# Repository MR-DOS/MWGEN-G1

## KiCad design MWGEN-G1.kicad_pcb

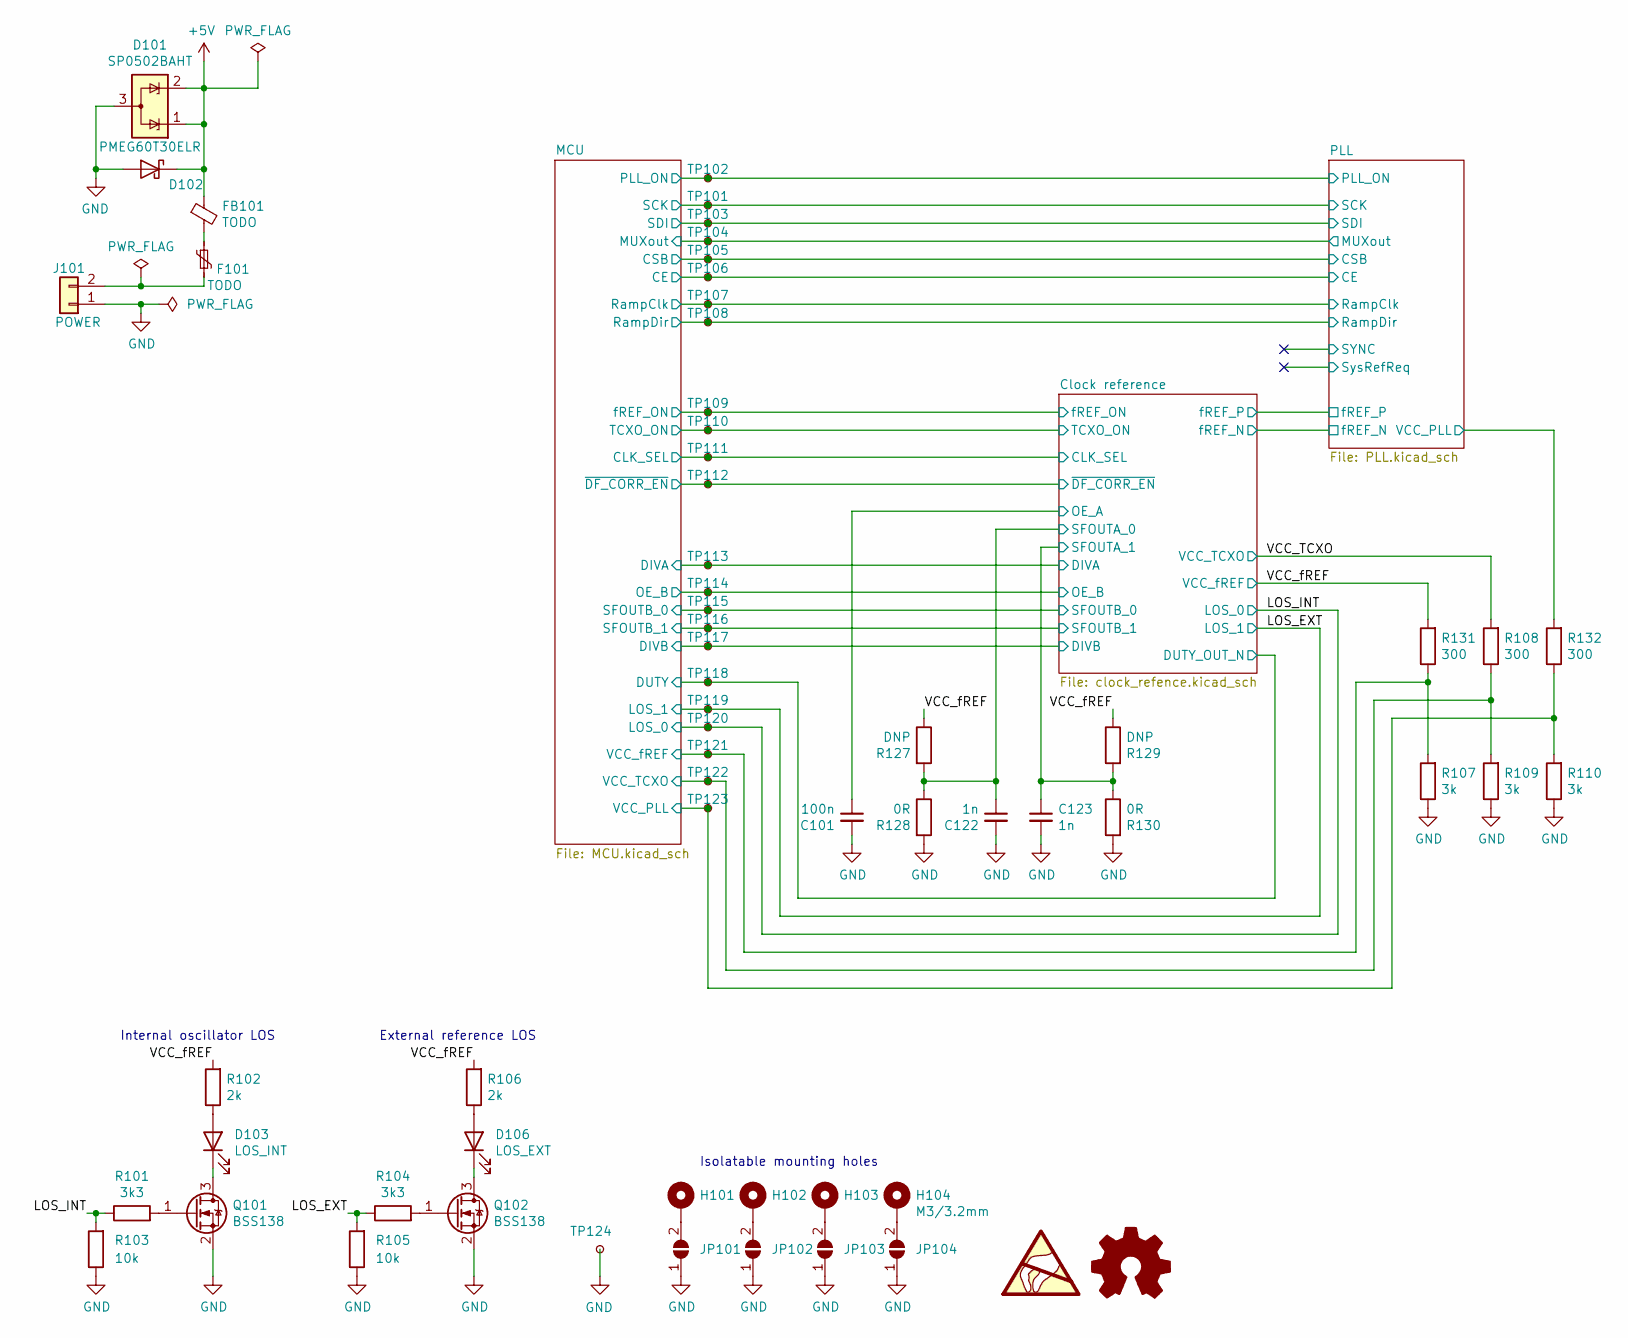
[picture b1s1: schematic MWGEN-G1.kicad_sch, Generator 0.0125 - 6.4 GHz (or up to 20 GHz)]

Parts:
C101: 100n; C_0603_1608Metric_Pad1.08x0.95mm_HandSolder
C122, C123: 1n; C_0603_1608Metric_Pad1.08x0.95mm_HandSolder
D101: SP0502BAHT; SOT-23
D102: PMEG60T30ELR; Nexperia_CFP3_SOD-123W
D103: LOS_INT; LED_0603_1608Metric_Pad1.05x0.95mm_HandSolder
D106: LOS_EXT; LED_0603_1608Metric_Pad1.05x0.95mm_HandSolder
F101: TODO; Fuse_2920_7451Metric_Pad2.10x5.45mm_HandSolder
FB101: TODO; L_0805_2012Metric_Pad1.05x1.20mm_HandSolder
H101, H102, H103, H104: M3/3.2mm; MountingHole_3.2mm_M3_Pad_Via
J101: POWER; PhoenixContact_MSTBA_2,5_2-G-5,08_1x02_P5.08mm_Horizontal
JP101, JP102, JP103, JP104: SolderJumper_2_Open; SolderJumper-2_P1.3mm_Open_TrianglePad1.0x1.5mm
Q101, Q102: BSS138; SOT-23
R101, R104: 3k3; R_0603_1608Metric_Pad0.98x0.95mm_HandSolder
R102, R106: 2k; R_0603_1608Metric_Pad0.98x0.95mm_HandSolder
R103, R105: 10k; R_0603_1608Metric_Pad0.98x0.95mm_HandSolder
R107, R109, R110: 3k; R_0603_1608Metric_Pad0.98x0.95mm_HandSolder
R108, R131, R132: 300; R_0603_1608Metric_Pad0.98x0.95mm_HandSolder
R127, R129: DNP; R_0603_1608Metric_Pad0.98x0.95mm_HandSolder
R128, R130: 0R; R_0603_1608Metric_Pad0.98x0.95mm_HandSolder
TP101, TP102, TP103, TP104, TP105, TP106, TP107, TP108, TP109, TP110, TP111, TP112, TP113, TP114, TP115, TP116, TP117, TP118, TP119, TP120, TP121, TP122, TP123, TP124: TestPoint_Small; TestPoint_Pad_D1.0mm

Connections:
+5V: D101.1 (K), D101.2 (K), D102.1 (K), FB101.1; also elsewhere on the board
/Clock reference/CLK_SEL: TP111.1; also elsewhere on the board
/Clock reference/DIVA: TP113.1; also elsewhere on the board
/Clock reference/DIVB: TP117.1; also elsewhere on the board
/Clock reference/Input Clocks/DUTY_OUT_N: TP118.1; also elsewhere on the board
/Clock reference/OE_A: C101.1; also elsewhere on the board
/Clock reference/OE_B: TP114.1; also elsewhere on the board
/Clock reference/SFOUTA_0: C122.1, R127.2, R128.1; also elsewhere on the board
/Clock reference/SFOUTA_1: C123.1, R129.2, R130.1; also elsewhere on the board
/Clock reference/SFOUTB_0: TP115.1; also elsewhere on the board
/Clock reference/SFOUTB_1: TP116.1; also elsewhere on the board
/Clock reference/TCXO_ON: TP110.1; also elsewhere on the board
/Clock reference/fREF_ON: TP109.1; also elsewhere on the board
/Clock reference/~DF_CORR_EN: TP112.1; also elsewhere on the board
/LOS_EXT: R104.1, R105.2, TP119.1; also elsewhere on the board
/LOS_INT: R101.1, R103.2, TP120.1; also elsewhere on the board
/MCU/CE: TP106.1; also elsewhere on the board
/MCU/CSB: TP105.1; also elsewhere on the board
/MCU/MUXout: TP104.1; also elsewhere on the board
/MCU/PLL_ON: TP102.1; also elsewhere on the board
/MCU/RampClk: TP107.1; also elsewhere on the board
/MCU/RampDir: TP108.1; also elsewhere on the board
/MCU/SCK: TP101.1; also elsewhere on the board
/MCU/SDI: TP103.1; also elsewhere on the board
/MCU/VCC_PLL: R110.2, R132.1, TP123.1; also elsewhere on the board
/MCU/VCC_TCXO: R108.1, R109.2, TP122.1; also elsewhere on the board
/MCU/VCC_fREF: R107.2, R131.1, TP121.1; also elsewhere on the board
/PLL/VCC_PLL: R132.2; also elsewhere on the board
/VCC_TCXO: R108.2; also elsewhere on the board
GND: C101.2, C122.2, C123.2, D101.3 (A), D102.2 (A), J101.1, JP101.1 (A), JP102.1 (A), JP103.1 (A), JP104.1 (A), Q101.2 (S), Q102.2 (S), R103.1, R105.1, R107.1, R109.1, R110.1, R128.2, R130.2, TP124.1; also elsewhere on the board
unnamed: D103.1 (K), Q101.3 (D)
unnamed: D103.2 (A), R102.1
unnamed: D106.1 (K), Q102.3 (D)
unnamed: D106.2 (A), R106.1
unnamed: F101.1, FB101.2
unnamed: F101.2, J101.2
unnamed: H101.1, JP101.2 (B)
unnamed: H102.1, JP102.2 (B)
unnamed: H103.1, JP103.2 (B)
unnamed: H104.1, JP104.2 (B)
unnamed: Q101.1 (G), R101.2
unnamed: Q102.1 (G), R104.2
VCC_fREF: R102.2, R106.2, R127.1, R129.1, R131.2; also elsewhere on the board

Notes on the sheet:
External reference LOS
Isolatable mounting holes
Internal oscillator LOS

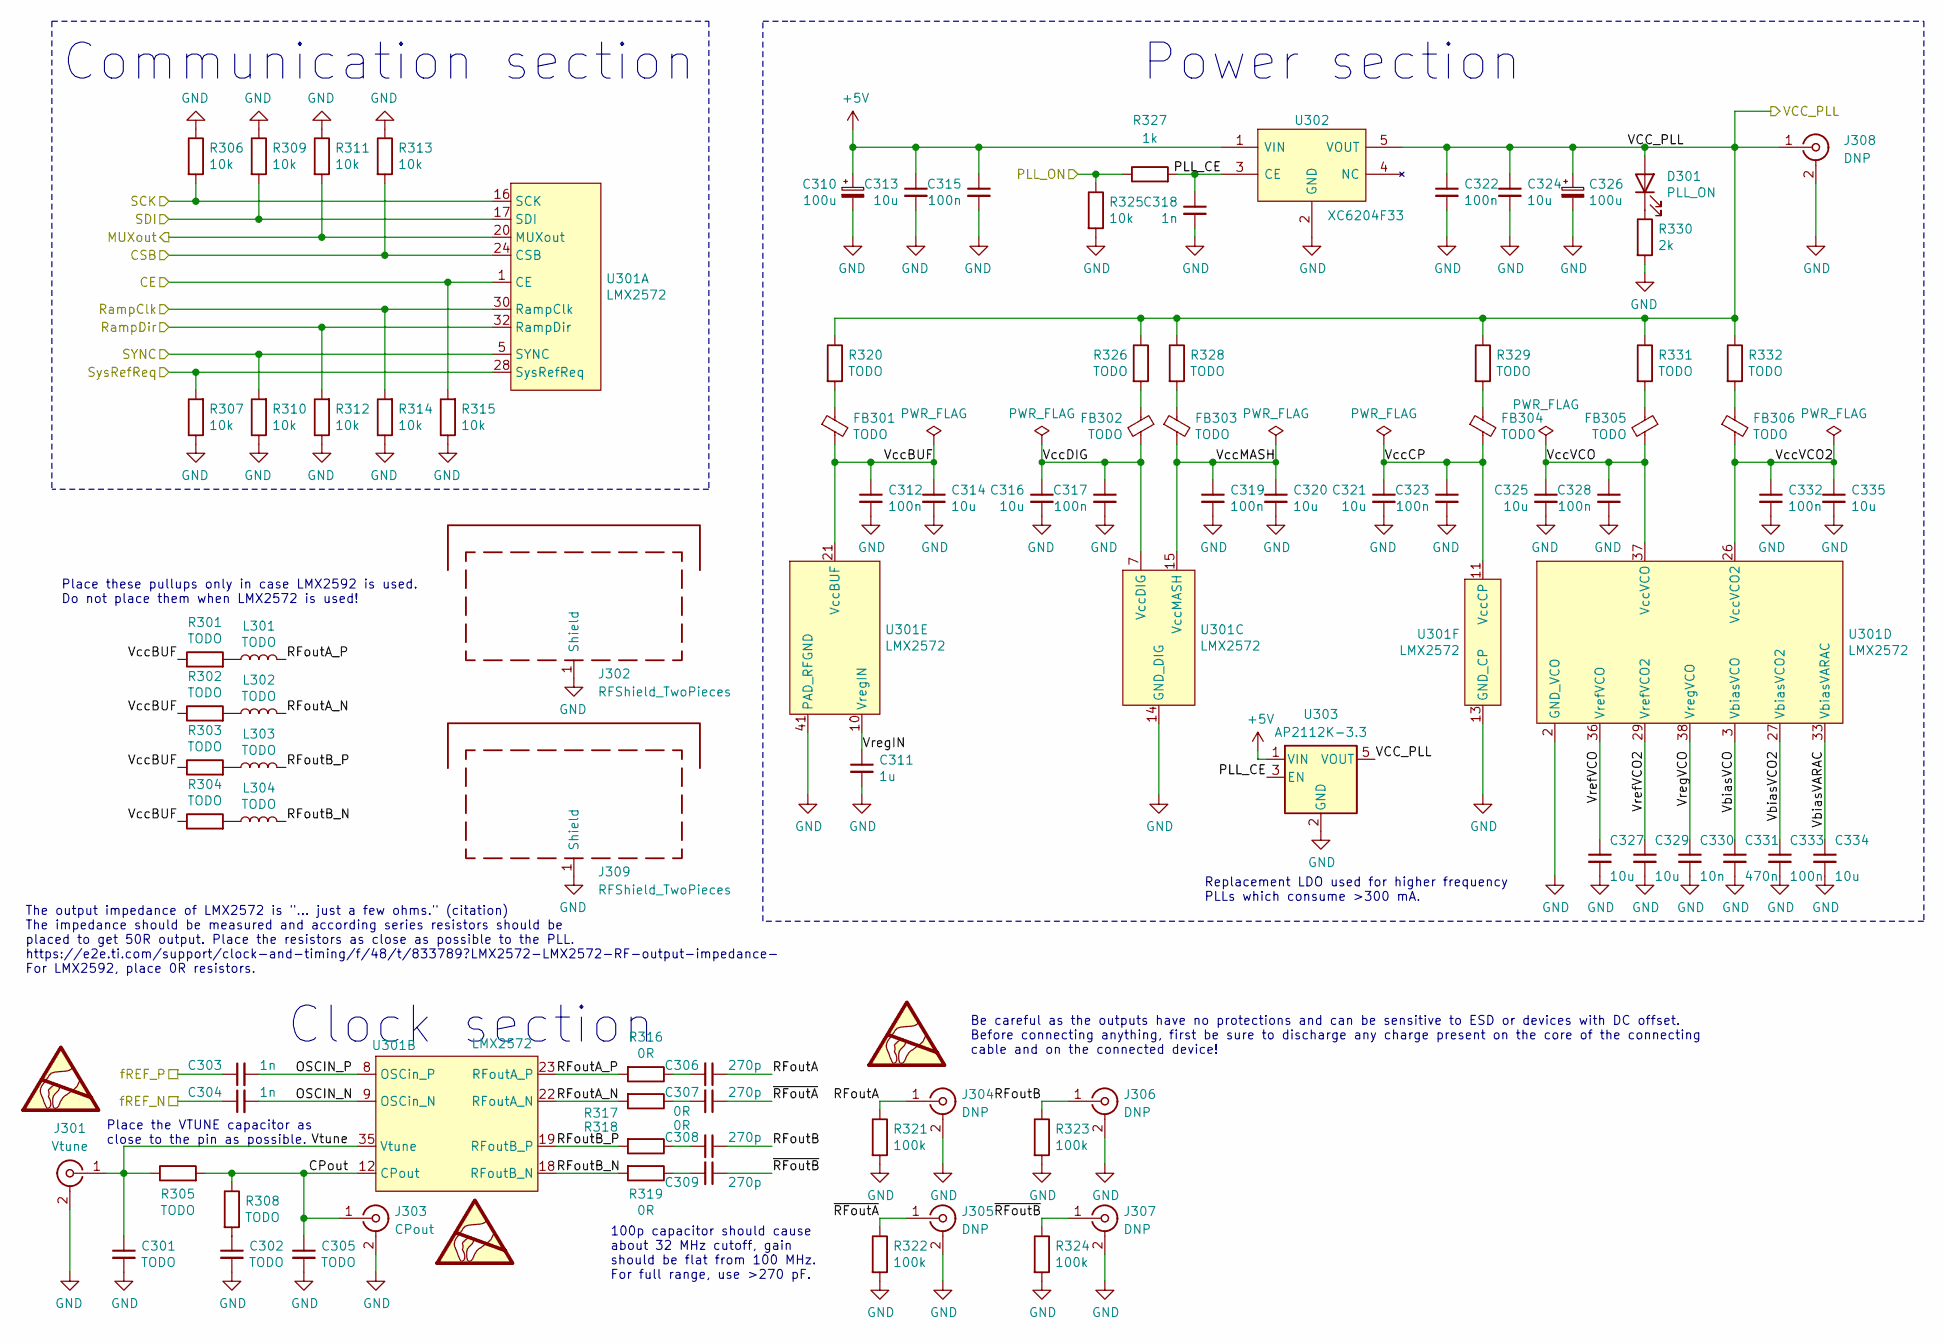
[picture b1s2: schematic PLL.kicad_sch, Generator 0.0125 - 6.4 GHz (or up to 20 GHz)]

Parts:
C301, C302, C305: TODO; C_0603_1608Metric_Pad1.08x0.95mm_HandSolder
C303, C304, C318: 1n; C_0603_1608Metric_Pad1.08x0.95mm_HandSolder
C306, C307, C308, C309: 270p; C_0603_1608Metric_Pad1.08x0.95mm_HandSolder
C310, C326: 100u; CP_Elec_6.3x5.8
C311: 1u; C_0603_1608Metric_Pad1.08x0.95mm_HandSolder
C312, C315, C317, C319, C322, C323, C328, C332, C333: 100n; C_0603_1608Metric_Pad1.08x0.95mm_HandSolder
C313, C314, C316, C320, C321, C324, C325, C327, C329, C334, C335: 10u; C_0805_2012Metric_Pad1.18x1.45mm_HandSolder
C330: 10n; C_0603_1608Metric_Pad1.08x0.95mm_HandSolder
C331: 470n; C_0603_1608Metric_Pad1.08x0.95mm_HandSolder
D301: PLL_ON; LED_0603_1608Metric_Pad1.05x0.95mm_HandSolder
FB301, FB302, FB303, FB304, FB305, FB306: TODO; L_0603_1608Metric_Pad1.05x0.95mm_HandSolder
J301: Vtune; U.FL_Molex_MCRF_73412-0110_Vertical
J302, J309: RFShield_TwoPieces; Laird_Technologies_BMI-S-205-F_38.10x25.40mm
J303: CPout; U.FL_Molex_MCRF_73412-0110_Vertical
J304, J305, J306, J307: DNP; SMA_rosenberger_hybrid
J308: DNP; U.FL_Molex_MCRF_73412-0110_Vertical
L301, L302, L303, L304: TODO; L_0603_1608Metric_Pad1.05x0.95mm_HandSolder
R301, R302, R303, R304, R305, R308, R320, R326, R328, R329, R331, R332: TODO; R_0603_1608Metric_Pad0.98x0.95mm_HandSolder
R306, R307, R309, R310, R311, R312, R313, R314, R315, R325: 10k; R_0603_1608Metric_Pad0.98x0.95mm_HandSolder
R316, R317, R318, R319: 0R; R_0603_1608Metric_Pad0.98x0.95mm_HandSolder
R321, R322, R323, R324: 100k; R_0603_1608Metric_Pad0.98x0.95mm_HandSolder
R327: 1k; R_0603_1608Metric_Pad0.98x0.95mm_HandSolder
R330: 2k; R_0603_1608Metric_Pad0.98x0.95mm_HandSolder
U301: LMX2572; QFN-40_EP_6x6_Pitch0.5mm_LMX2572
U302: XC6204F33; SOT-89-5_Handsoldering
U303: AP2112K-3.3; SOT-23-5

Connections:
+5V: C310.1, C313.1, C315.1, U302.1 (VIN), U303.1 (VIN); also elsewhere on the board
/Clock reference/fREF_N: C304.1; also elsewhere on the board
/Clock reference/fREF_P: C303.1; also elsewhere on the board
/MCU/CE: R315.2, U301.1 (CE); also elsewhere on the board
/MCU/CSB: R313.2, U301.24 (CSB); also elsewhere on the board
/MCU/MUXout: R311.2, U301.20 (MUXout); also elsewhere on the board
/MCU/PLL_ON: R325.1, R327.1; also elsewhere on the board
/MCU/RampClk: R314.2, U301.30 (RampClk); also elsewhere on the board
/MCU/RampDir: R312.2, U301.32 (RampDir); also elsewhere on the board
/MCU/SCK: R306.2, U301.16 (SCK); also elsewhere on the board
/MCU/SDI: R309.2, U301.17 (SDI); also elsewhere on the board
/PLL/CPout: C305.1, J303.1 (In), R305.2, R308.1, U301.12 (CPout)
/PLL/OSCIN_N: C304.2, U301.9 (OSCin_N)
/PLL/OSCIN_P: C303.2, U301.8 (OSCin_P)
/PLL/RFoutA: C306.1, J304.1 (In), R321.1
/PLL/RFoutA_N: L302.2, R317.2, U301.22 (RFoutA_N)
/PLL/RFoutA_P: L301.2, R316.2, U301.23 (RFoutA_P)
/PLL/RFoutB: C308.1, J306.1 (In), R323.1
/PLL/RFoutB_N: L304.2, R319.2, U301.18 (RFoutB_N)
/PLL/RFoutB_P: L303.2, R318.2, U301.19 (RFoutB_P)
/PLL/SYNC: R310.2, U301.5 (SYNC)
/PLL/SysRefReq: R307.2, U301.28 (SysRefReq)
/PLL/VCC_PLL: C322.1, C324.1, C326.1, D301.2 (A), J308.1 (In), R320.1, R326.1, R328.1, R329.1, R331.1, R332.1, U302.5 (VOUT), U303.5 (VOUT); also elsewhere on the board
/PLL/VbiasVARAC: C334.1, U301.33 (VbiasVARAC)
/PLL/VbiasVCO: C331.1, U301.3 (VbiasVCO)
/PLL/VbiasVCO2: C333.1, U301.27 (VbiasVCO2)
/PLL/VccBUF: C312.1, C314.1, FB301.2, R301.1, R302.1, R303.1, R304.1, U301.21 (VccBUF)
/PLL/VccCP: C321.1, C323.1, FB304.2, U301.11 (VccCP)
/PLL/VccDIG: C316.1, C317.1, FB302.2, U301.7 (VccDIG)
/PLL/VccMASH: C319.1, C320.1, FB303.2, U301.15 (VccMASH)
/PLL/VccVCO: C325.1, C328.1, FB305.2, U301.37 (VccVCO)
/PLL/VccVCO2: C332.1, C335.1, FB306.2, U301.26 (VccVCO2)
/PLL/VrefVCO: C327.1, U301.36 (VrefVCO)
/PLL/VrefVCO2: C329.1, U301.29 (VrefVCO2)
/PLL/VregIN: C311.1, U301.10 (VregIN)
/PLL/VregVCO: C330.1, U301.38 (VregVCO)
/PLL/Vtune: C301.1, J301.1 (In), R305.1, U301.35 (Vtune)
/PLL/~RFoutA: C307.1, J305.1 (In), R322.1
/PLL/~RFoutB: C309.1, J307.1 (In), R324.1
GND: C301.2, C302.2, C305.2, C310.2, C311.2, C312.2, C313.2, C314.2, C315.2, C316.2, C317.2, C318.2, C319.2, C320.2, C321.2, C322.2, C323.2, C324.2, C325.2, C326.2, C327.2, C328.2, C329.2, C330.2, C331.2, C332.2, C333.2, C334.2, C335.2, J301.2 (Ext), J302.1 (Shield), J303.2 (Ext), J304.2 (Ext), J305.2 (Ext), J306.2 (Ext), J307.2 (Ext), J308.2 (Ext), J309.1 (Shield), R306.1, R307.1, R309.1, R310.1, R311.1, R312.1, R313.1, R314.1, R315.1, R321.2, R322.2, R323.2, R324.2, R325.2, R330.2, U301.2 (GND_VCO), U301.4 (GND_VCO), U301.6 (GND_DIG), U301.13 (GND_CP), U301.14 (GND_DIG), U301.25 (GND_VCO), U301.31 (GND_VCO), U301.34 (GND_VCO), U301.39 (GND_VCO), U301.40 (GND_DIG), U301.41 (PAD_RFGND), U302.2 (GND), U303.2 (GND); also elsewhere on the board
unnamed: C302.1, R308.2
unnamed: C306.2, R316.1
unnamed: C307.2, R317.1
unnamed: C308.2, R318.1
unnamed: C309.2, R319.1
unnamed: C318.1, R327.2, U302.3 (CE), U303.3 (EN)
unnamed: D301.1 (K), R330.1
unnamed: FB301.1, R320.2
unnamed: FB302.1, R326.2
unnamed: FB303.1, R328.2
unnamed: FB304.1, R329.2
unnamed: FB305.1, R331.2
unnamed: FB306.1, R332.2
unnamed: L301.1, R301.2
unnamed: L302.1, R302.2
unnamed: L303.1, R303.2
unnamed: L304.1, R304.2

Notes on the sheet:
The output impedance of LMX2572 is "... just a few ohms." (citation) The impedance should be measured and according series resistors should be placed to get 50R output. Place the resistors as close as possible to the PLL. https://e2e.ti.com/support/clock-and-timing/f/48/t/833789?LMX2572-LMX2572-RF-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
Clock section
100p capacitor should cause about 32 MHz cutoff, gain should be flat from 100 MHz. For full range, use >270 pF.
Place these pullups only in case LMX2592 is used. Do not place them when LMX2572 is used!
Replacement LDO used for higher frequency PLLs which consume >300 mA.
Be careful as the outputs have no protections and can be sensitive to ESD or devices with DC offset. Before connecting anything, first be sure to discharge any charge present on the core of the connecting cable and on the connected device!
Place the VTUNE capacitor as close to the pin as possible.
Communication section
Power section

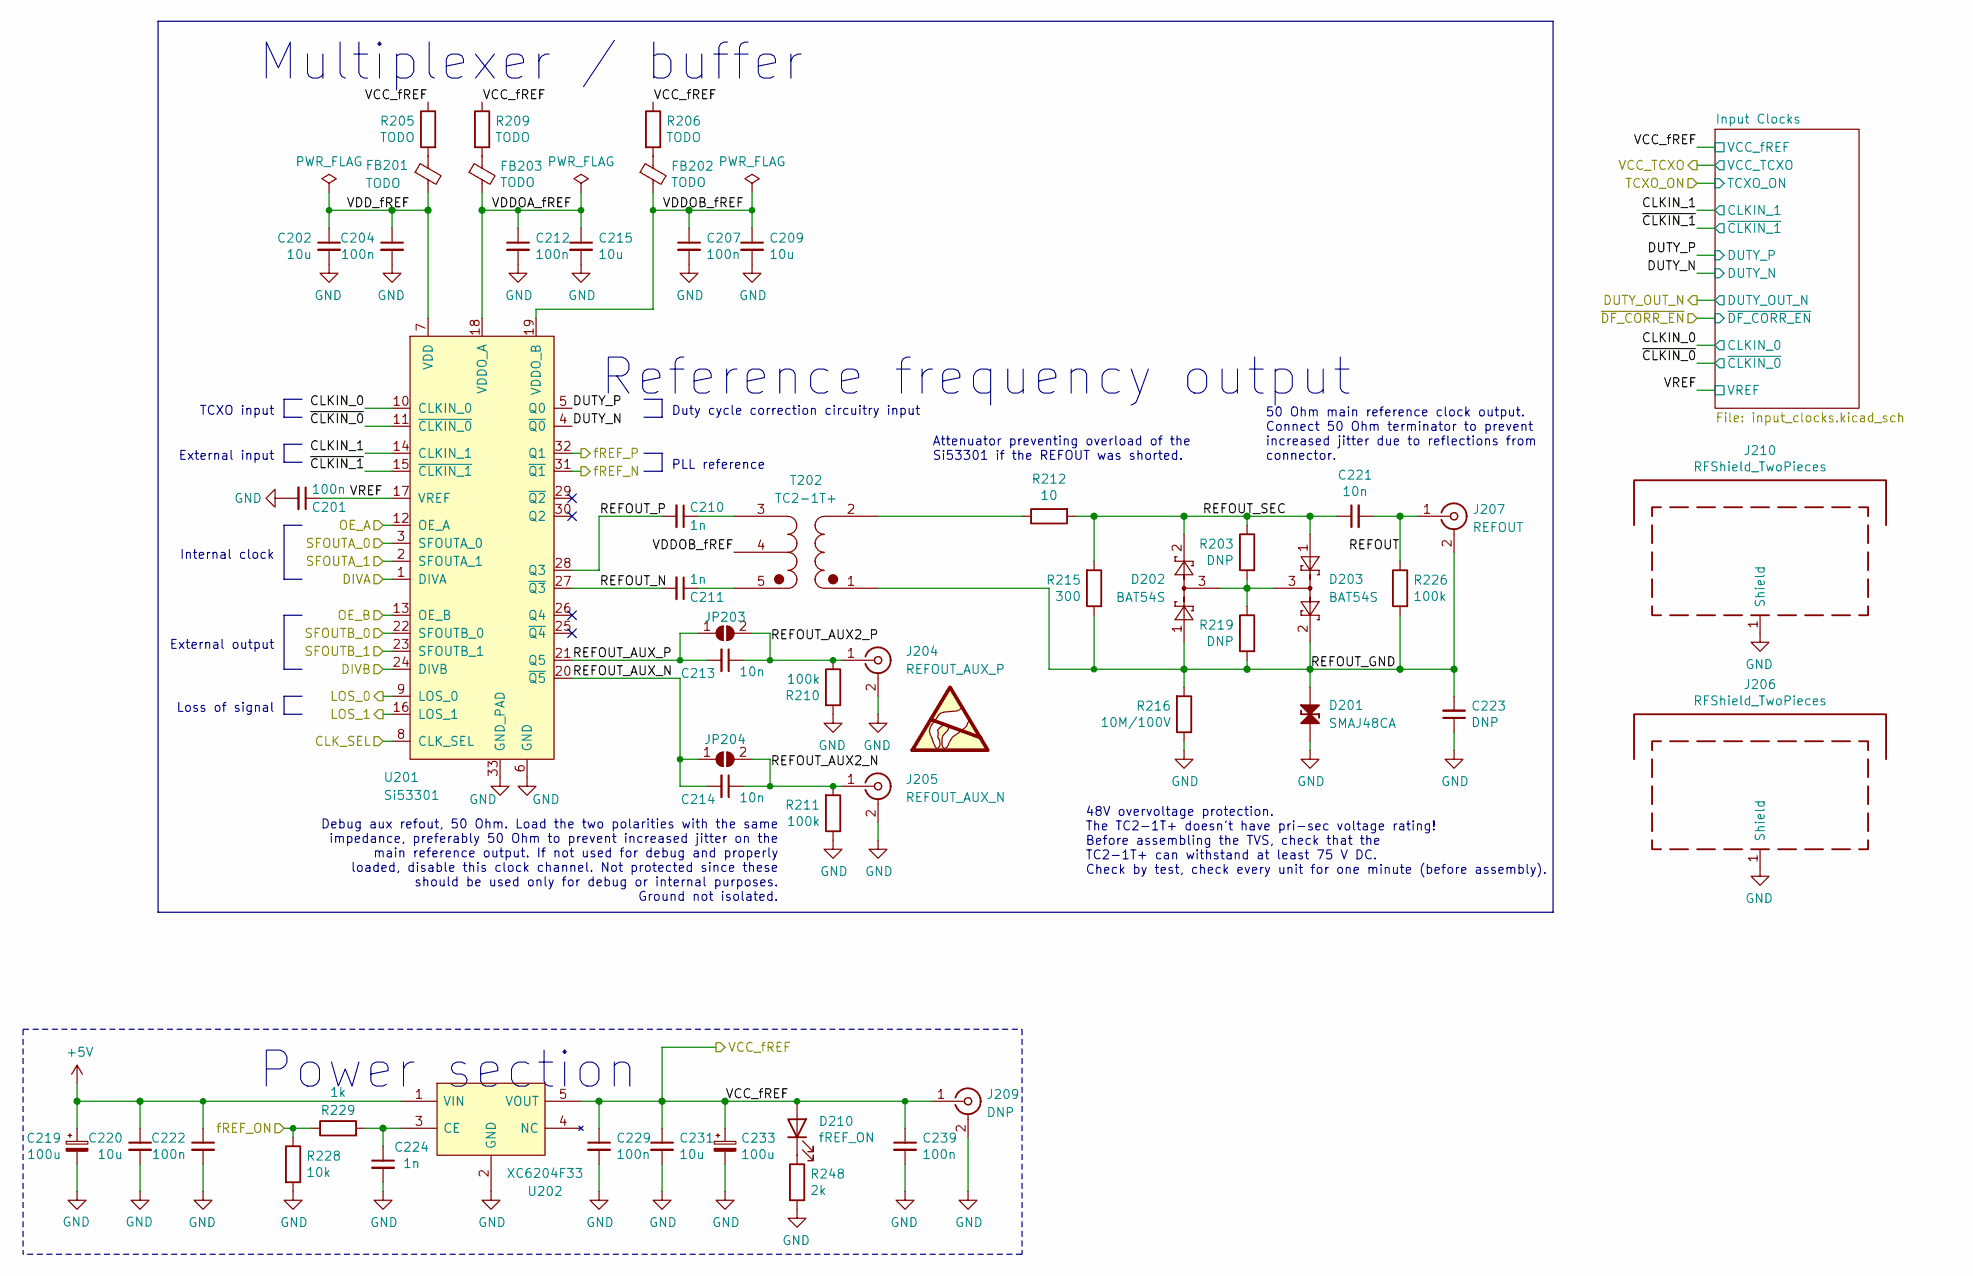
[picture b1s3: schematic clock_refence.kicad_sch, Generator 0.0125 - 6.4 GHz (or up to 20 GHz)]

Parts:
C201, C204, C207, C212, C222, C229, C239: 100n; C_0603_1608Metric_Pad1.08x0.95mm_HandSolder
C202, C209, C215, C220, C231: 10u; C_0805_2012Metric_Pad1.18x1.45mm_HandSolder
C210, C211, C224: 1n; C_0603_1608Metric_Pad1.08x0.95mm_HandSolder
C213, C214, C221: 10n; C_0603_1608Metric_Pad1.08x0.95mm_HandSolder
C219, C233: 100u; CP_Elec_6.3x5.8
C223: DNP; C_0603_1608Metric_Pad1.08x0.95mm_HandSolder
D201: SMAJ48CA; D_SMA_TVS
D202, D203: BAT54S; SOT-23
D210: fREF_ON; LED_0603_1608Metric_Pad1.05x0.95mm_HandSolder
FB201, FB202, FB203: TODO; L_0603_1608Metric_Pad1.05x0.95mm_HandSolder
J204: REFOUT_AUX_P; U.FL_Molex_MCRF_73412-0110_Vertical
J205: REFOUT_AUX_N; U.FL_Molex_MCRF_73412-0110_Vertical
J206, J210: RFShield_TwoPieces; Laird_Technologies_BMI-S-205-F_38.10x25.40mm
J207: REFOUT; SMA_rosenberger_hybrid
J209: DNP; U.FL_Molex_MCRF_73412-0110_Vertical
JP203, JP204: SolderJumper_2_Open; SolderJumper-2_P1.3mm_Open_RoundedPad1.0x1.5mm
R203, R219: DNP; R_0603_1608Metric_Pad0.98x0.95mm_HandSolder
R205, R206, R209: TODO; R_0603_1608Metric_Pad0.98x0.95mm_HandSolder
R210, R211, R226: 100k; R_0603_1608Metric_Pad0.98x0.95mm_HandSolder
R212: 10; R_0603_1608Metric_Pad0.98x0.95mm_HandSolder
R215: 300; R_0603_1608Metric_Pad0.98x0.95mm_HandSolder
R216: 10M/100V; R_1206_3216Metric_Pad1.30x1.75mm_HandSolder
R228: 10k; R_0603_1608Metric_Pad0.98x0.95mm_HandSolder
R229: 1k; R_0603_1608Metric_Pad0.98x0.95mm_HandSolder
R248: 2k; R_0603_1608Metric_Pad0.98x0.95mm_HandSolder
T202: TC2-1T+; Transformer_MiniCircuits_AT224-1A
U201: Si53301; QFN-32_EP_5x5_Pitch0.5mm_Si53301
U202: XC6204F33; SOT-89-5_Handsoldering

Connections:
+5V: C219.1, C220.1, C222.1, U202.1 (VIN); also elsewhere on the board
/Clock reference/CLKIN_0: U201.10 (CLKIN_0); also elsewhere on the board
/Clock reference/CLKIN_1: U201.14 (CLKIN_1); also elsewhere on the board
/Clock reference/CLK_SEL: U201.8 (CLK_SEL); also elsewhere on the board
/Clock reference/DIVA: U201.1 (DIVA); also elsewhere on the board
/Clock reference/DIVB: U201.24 (DIVB); also elsewhere on the board
/Clock reference/DUTY_N: U201.4 (~Q0); also elsewhere on the board
/Clock reference/DUTY_P: U201.5 (Q0); also elsewhere on the board
/Clock reference/OE_A: U201.12 (OE_A); also elsewhere on the board
/Clock reference/OE_B: U201.13 (OE_B); also elsewhere on the board
/Clock reference/REFOUT: C221.2, J207.1 (In), R226.1
/Clock reference/REFOUT_AUX2_N: C214.1, J205.1 (In), JP204.2 (B), R211.2
/Clock reference/REFOUT_AUX2_P: C213.1, J204.1 (In), JP203.2 (B), R210.1
/Clock reference/REFOUT_AUX_N: C214.2, JP204.1 (A), U201.20 (~Q5)
/Clock reference/REFOUT_AUX_P: C213.2, JP203.1 (A), U201.21 (Q5)
/Clock reference/REFOUT_GND: C223.2, D201.2 (A), D202.1, D203.2, J207.2 (Ext), R215.1, R216.2, R219.2, R226.2, T202.1 (AA)
/Clock reference/REFOUT_N: C211.2, U201.27 (~Q3)
/Clock reference/REFOUT_P: C210.2, U201.28 (Q3)
/Clock reference/REFOUT_SEC: C221.1, D202.2, D203.1, R203.1, R212.2, R215.2
/Clock reference/SFOUTA_0: U201.3 (SFOUTA_0); also elsewhere on the board
/Clock reference/SFOUTA_1: U201.2 (SFOUTA_1); also elsewhere on the board
/Clock reference/SFOUTB_0: U201.22 (SFOUTB_0); also elsewhere on the board
/Clock reference/SFOUTB_1: U201.23 (SFOUTB_1); also elsewhere on the board
/Clock reference/VDDOA_fREF: C212.1, C215.1, FB203.2, U201.18 (VDDO_A)
/Clock reference/VDDOB_fREF: C207.1, C209.1, FB202.2, T202.4 (SC), U201.19 (VDDO_B)
/Clock reference/VDD_fREF: C202.1, C204.1, FB201.2, U201.7 (VDD)
/Clock reference/VREF: C201.1, U201.17 (VREF); also elsewhere on the board
/Clock reference/fREF_N: U201.31 (~Q1); also elsewhere on the board
/Clock reference/fREF_ON: R228.1, R229.1; also elsewhere on the board
/Clock reference/fREF_P: U201.32 (Q1); also elsewhere on the board
/Clock reference/~CLKIN_0: U201.11 (~CLKIN_0); also elsewhere on the board
/Clock reference/~CLKIN_1: U201.15 (~CLKIN_1); also elsewhere on the board
/LOS_EXT: U201.16 (LOS_1); also elsewhere on the board
/LOS_INT: U201.9 (LOS_0); also elsewhere on the board
GND: C201.2, C202.2, C204.2, C207.2, C209.2, C212.2, C215.2, C219.2, C220.2, C222.2, C223.1, C224.2, C229.2, C231.2, C233.2, C239.2, D201.1 (K), J204.2 (Ext), J205.2 (Ext), J206.1 (Shield), J209.2 (Ext), J210.1 (Shield), R210.2, R211.1, R216.1, R228.2, R248.2, U201.6 (GND), U201.33 (GND_PAD), U202.2 (GND); also elsewhere on the board
unnamed: C210.1, T202.3 (SA)
unnamed: C211.1, T202.5 (SB)
unnamed: C224.1, R229.2, U202.3 (CE)
unnamed: D202.3, D203.3, R203.2, R219.1
unnamed: D210.1 (K), R248.1
unnamed: FB201.1, R205.2
unnamed: FB202.1, R206.2
unnamed: FB203.1, R209.2
unnamed: R212.1, T202.2 (AB)
VCC_fREF: C229.1, C231.1, C233.1, C239.1, D210.2 (A), J209.1 (In), R205.1, R206.1, R209.1, U202.5 (VOUT); also elsewhere on the board

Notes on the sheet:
External output
Multiplexer / buffer
Duty cycle correction circuitry input
TCXO input
Reference frequency output
Power section
50 Ohm main reference clock output. Connect 50 Ohm terminator to prevent increased jitter due to reflections from connector.
Attenuator preventing overload of the Si53301 if the REFOUT was shorted.
External input
Debug aux refout, 50 Ohm. Load the two polarities with the same impedance, preferably 50 Ohm to prevent increased jitter on the main reference output. If not used for debug and properly loaded, disable this clock channel. Not protected since these should be used only for debug or internal purposes.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
PLL reference
48V overvoltage protection. The TC2-1T+ doesn't have pri-sec voltage rating! Before assembling the TVS, check that the TC2-1T+ can withstand at least 75 V DC. Check by test, check every unit for one minute (before assembly).
Loss of signal
Internal clock

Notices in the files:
parts and their libraries:
Copyright 2021 Accelerated Designs. All rights reserved.
